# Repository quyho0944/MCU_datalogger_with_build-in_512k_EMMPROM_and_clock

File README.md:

# MCU Datalogger with Built-in 512k EEPROM & RTC Clock

## 📝 Giới thiệu dự án
Dự án thiết kế phần cứng **MCU Datalogger** được thực hiện trên nền tảng **KiCad**. Hệ thống được tối ưu hóa cho các ứng dụng thu thập, giám sát và lưu trữ dữ liệu từ cảm biến hoặc các thiết bị công nghiệp theo thời gian thực (Real-time Data Logging). 

Bo mạch được thiết kế nhỏ gọn, độ nhiễu thấp, sẵn sàng cho các ứng dụng thực tế đòi hỏi độ tin cậy cao trong việc lưu trữ dữ liệu dài hạn.

---

## 🚀 Tính năng nổi bật
* **Bộ nhớ lưu trữ dung lượng lớn:** Tích hợp chip nhớ ngoại vi **EEPROM 512k**, cho phép lưu trữ hàng ngàn bản ghi dữ liệu một cách an toàn. Dữ liệu không bị mất khi hệ thống mất nguồn điện đột ngột (Non-volatile memory).
* **Thời gian thực chính xác:** Tích hợp mạch đồng hồ thời gian thực (**RTC Clock**), tự động gắn nhãn thời gian (Timestamp: Ngày/Tháng/Năm/Giờ/Phút/Giây) chính xác cho từng gói dữ liệu thu thập được.
* **Thiết kế phần cứng chuyên nghiệp:** Sơ đồ nguyên lý (Schematic) và thiết kế mạch in (PCB Layout) được tối ưu hóa hoàn toàn trên phần mềm **KiCad**.

---

## 🛠️ Thành phần linh kiện chính
* **MCU:** ATmega328P-AU
* **Storage:** EEPROM 512k (Giao tiếp I2C)
* **Clock:** RTC Module DS1337S+
* **Nguồn cấp:** Tích hợp mạch bảo vệ và hạ áp ổn định.

---

## 📂 Cấu trúc thư mục dự án
```text
├── Hardware/          # Chứa file thiết kế KiCad (Schematic, PCB, 3D Model)
├── Firmware/          # Mã nguồn chương trình cho MCU (nếu có)
├── Docs/              # Tài liệu kỹ thuật, Datasheet linh kiện
└── README.md          # File giới thiệu dự án

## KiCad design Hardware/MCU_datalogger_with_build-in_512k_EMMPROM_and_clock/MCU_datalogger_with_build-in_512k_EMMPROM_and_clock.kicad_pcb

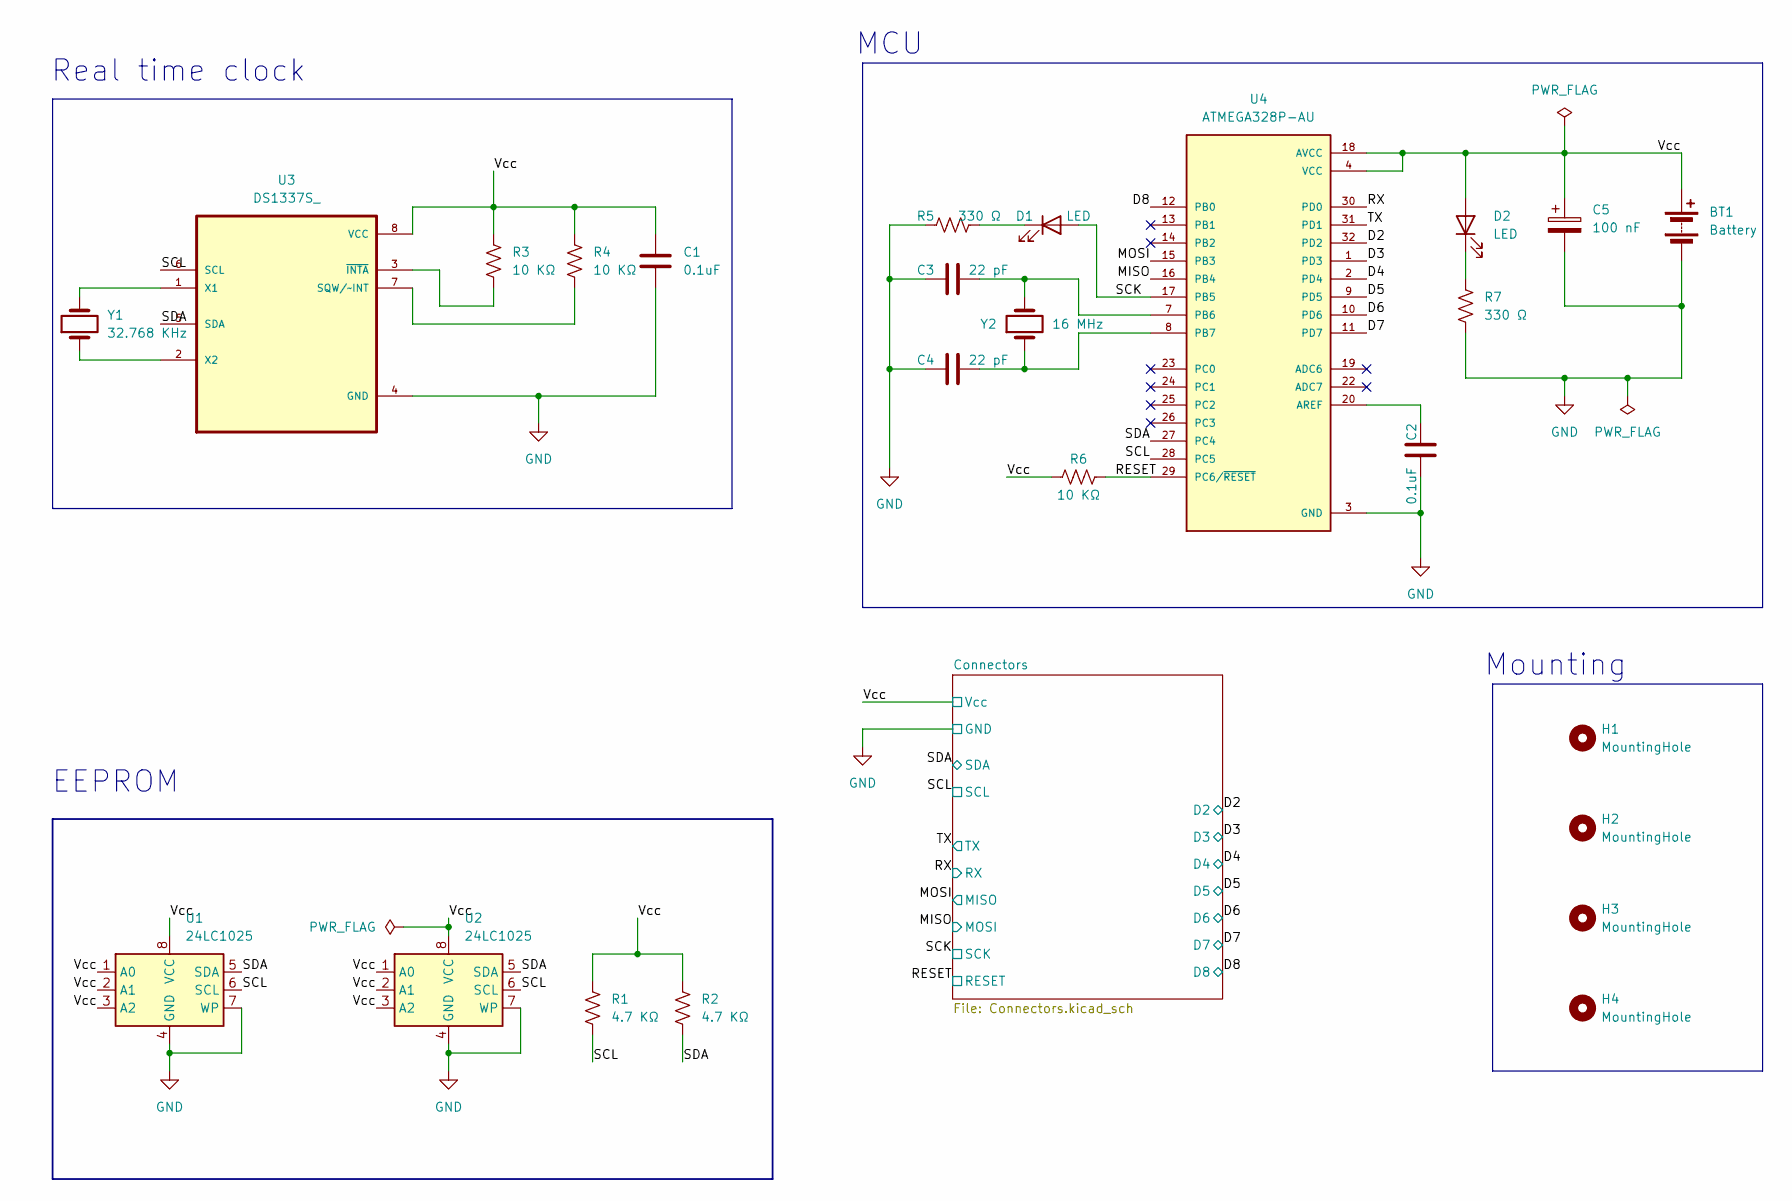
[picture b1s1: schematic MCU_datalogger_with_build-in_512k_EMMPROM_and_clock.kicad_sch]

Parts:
BT1: Battery; PinHeader_1x02_P2.54mm_Vertical
C1, C2: 0.1uF; C_0805_2012Metric
C3, C4: 22 pF; C_0805_2012Metric
C5: 100 nF; C_0805_2012Metric
D1, D2: LED; LED_0805_2012Metric
H1, H2, H3, H4: MountingHole; MountingHole_2.1mm
R1, R2: 4.7 KΩ; R_0805_2012Metric
R3, R4, R6: 10 KΩ; R_0805_2012Metric
R5, R7: 330 Ω; R_0805_2012Metric
U1, U2: 24LC1025; SOIC-8_5.3x5.3mm_P1.27mm
U3: DS1337S_; SOIC127P600X175-8N
U4: ATMEGA328P-AU; QFP80P900X900X120-32N; PARTREV 8271A
Y1: 32.768 KHz; Crystal_SMD_5032-2Pin_5.0x3.2mm_HandSoldering
Y2: 16 MHz; Crystal_SMD_5032-2Pin_5.0x3.2mm_HandSoldering

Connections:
/D2: U4.32 (PD2); also elsewhere on the board
/D3: U4.1 (PD3); also elsewhere on the board
/D4: U4.2 (PD4); also elsewhere on the board
/D5: U4.9 (PD5); also elsewhere on the board
/D6: U4.10 (PD6); also elsewhere on the board
/D7: U4.11 (PD7); also elsewhere on the board
/D8: U4.12 (PB0); also elsewhere on the board
/MISO: U4.16 (PB4); also elsewhere on the board
/MOSI: U4.15 (PB3); also elsewhere on the board
/RESET: R6.2, U4.29 (PC6/~RESET); also elsewhere on the board
/RX: U4.30 (PD0); also elsewhere on the board
/SCK: D1.2 (A), U4.17 (PB5); also elsewhere on the board
/SCL: R1.2, U1.6 (SCL), U2.6 (SCL), U3.6 (SCL), U4.28 (PC5); also elsewhere on the board
/SDA: R2.2, U1.5 (SDA), U2.5 (SDA), U3.5 (SDA), U4.27 (PC4); also elsewhere on the board
/TX: U4.31 (PD1); also elsewhere on the board
GND: BT1.2 (-), C1.2, C2.2, C3.1, C4.1, C5.2, R5.1, R7.1, U1.4 (GND), U1.7 (WP), U2.4 (GND), U2.7 (WP), U3.4 (GND), U4.3 (GND), U4.5 (GND), U4.21 (GND); also elsewhere on the board
unnamed: D1.1 (K), R5.2
unnamed: D2.1 (K), R7.2
unnamed: R4.2, U3.7 (SQW/~INT)
unnamed: U3.1 (X1), Y1.2
unnamed: U3.2 (X2), Y1.1
unnamed: R3.2, U3.3 (~INTA)
unnamed: C2.1, U4.20 (AREF)
unnamed: C3.2, U4.7 (PB6), Y2.2
unnamed: C4.2, U4.8 (PB7), Y2.1
VCC: BT1.1 (+), C1.1, C5.1, D2.2 (A), R1.1, R2.1, R3.1, R4.1, R6.1, U1.1 (A0), U1.2 (A1), U1.3 (A2), U1.8 (VCC), U2.1 (A0), U2.2 (A1), U2.3 (A2), U2.8 (VCC), U3.8 (VCC), U4.4 (VCC), U4.6 (VCC), U4.18 (AVCC); also elsewhere on the board

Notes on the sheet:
Mounting
MCU
EEPROM
Real time clock

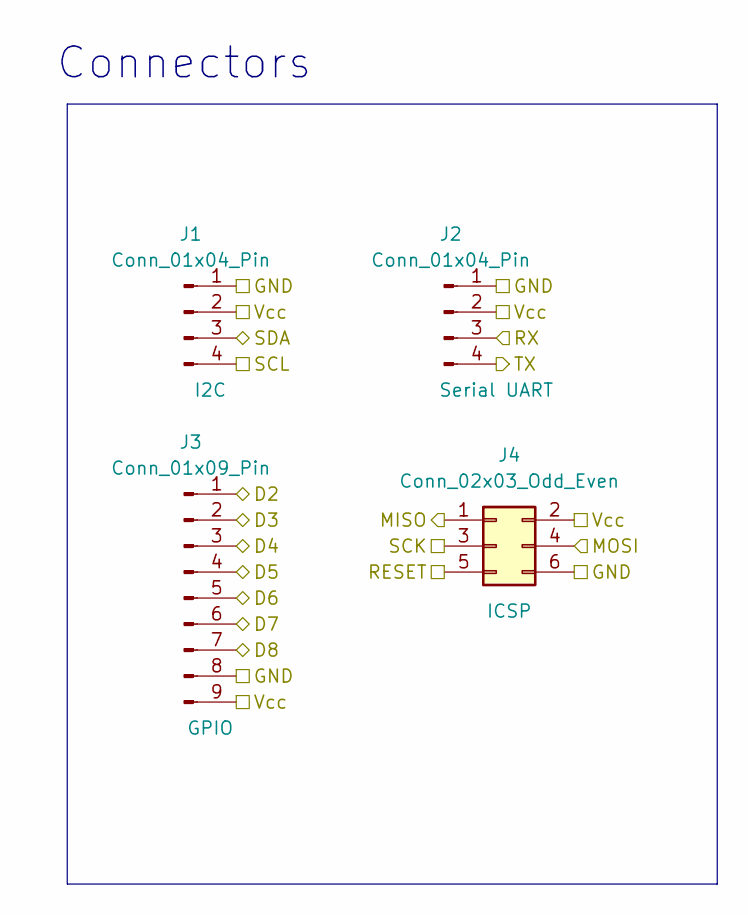
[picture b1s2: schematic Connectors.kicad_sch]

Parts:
J1, J2: Conn_01x04_Pin; PinHeader_1x04_P2.54mm_Vertical
J3: Conn_01x09_Pin; PinHeader_1x09_P2.54mm_Vertical
J4: Conn_02x03_Odd_Even; PinHeader_2x03_P2.54mm_Vertical

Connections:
/D2: J3.1; also elsewhere on the board
/D3: J3.2; also elsewhere on the board
/D4: J3.3; also elsewhere on the board
/D5: J3.4; also elsewhere on the board
/D6: J3.5; also elsewhere on the board
/D7: J3.6; also elsewhere on the board
/D8: J3.7; also elsewhere on the board
/MISO: J4.4; also elsewhere on the board
/MOSI: J4.1; also elsewhere on the board
/RESET: J4.5; also elsewhere on the board
/RX: J2.3; also elsewhere on the board
/SCK: J4.3; also elsewhere on the board
/SCL: J1.4; also elsewhere on the board
/SDA: J1.3; also elsewhere on the board
/TX: J2.4; also elsewhere on the board
GND: J1.1, J2.1, J3.8, J4.6; also elsewhere on the board
VCC: J1.2, J2.2, J3.9, J4.2; also elsewhere on the board

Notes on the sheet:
Connectors

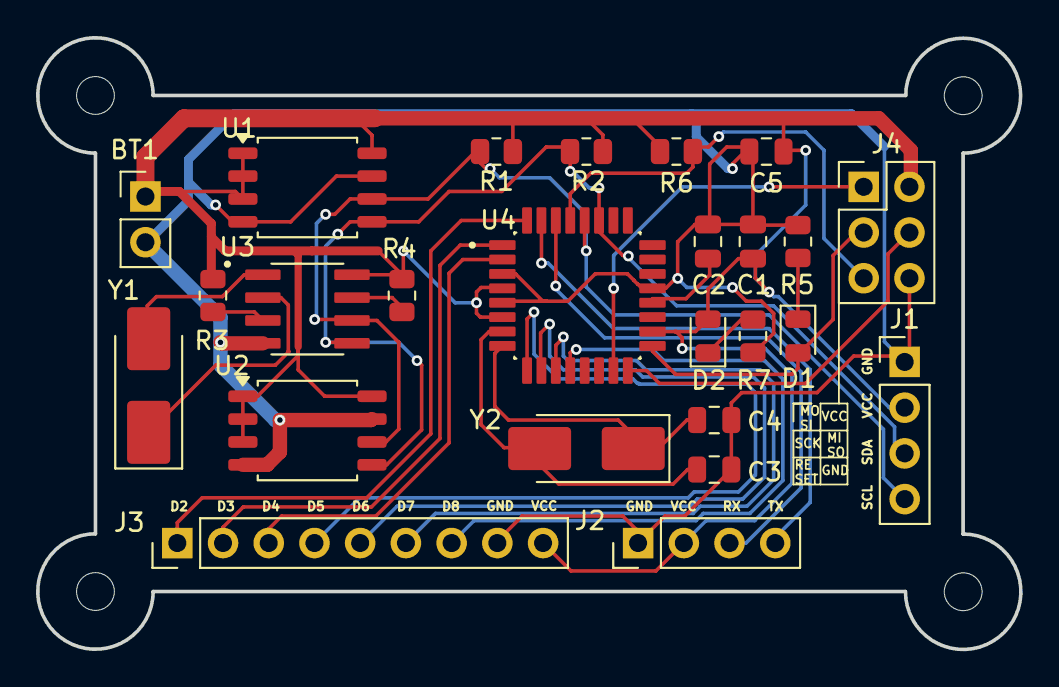
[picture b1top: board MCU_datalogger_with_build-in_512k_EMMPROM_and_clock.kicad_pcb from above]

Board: 2 copper layers, 54.6 x 34.0 mm, 29 parts (0 on the bottom side), 26 nets.

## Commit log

2026-06-01 upload all files and folders
